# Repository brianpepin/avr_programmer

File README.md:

# AVR Programmer
Eagle files and gerbers for a programmer designed for Microchip's series of AVR microcontrollers. There is also a KiCad variant in the kicad directory, but I haven't tried it yet.  It was ported from Eagle and I re-routed the board.

## Overview
Microchip's series of AVR chips are simple 8 bit microcontrollers often used in Arduino boards. This programmer board can be used to program fuses and flash for bare AVR chips.

## Features

* Compatible with USBASP firmware and features, including slow clock.
* Selectable target voltage of 3.3v, 5v, or target provided (1.8v - 5.5v).
* Built-in serial to USB converter.
* Board can remain connected to target after programming.
* USB-C interface to PC with full ESD and overload protection.

## Design

This board is based on the hardware design for [USBASP](https://www.fischl.de/usbasp/) and is 100% compatible wth the USBASP firmware. I designed it to support different target voltages (namely 3.3v) and wanted built-in serial IO so I could connect a single connector to boards I design.

The board shows up as two USB devices: a FTDI serial port and a USBASP programmer.  There is an on-board USB hub that exposes both devices.  Target voltage is selectable through the VTARG switch and has three values:

1. 5V (left): Provide 5 volts as power and logic levels to the target board.
1. Float (middle): Adapt to whatever voltage the target board is using.
1. 3.3V (right): Provide 3.3 volts as power and logic levels to the target board.

If your board provides voltage of its own make sure you keep VTARG in the middle position.

The different voltage levels are shifted through an array of level shifters.  This circuit will change direction of the signals if PGM is bridged, which allows for initial programming of the board. All connections other than TXD and RXD also go to a high-impedance state whenever the red programming light is off (I reuse that signal line so I don't need any modifications to the USBASP firmware). Signal direction and tri-state is controlled by discrete logic, again so no USBASP mods are needed.  The level shifters I'm using go to high-impedance state when VCCA or VCCB is grounded.  This is handled by a push-pull pair of mosfets driven by discrete logic.

## Programming

Once the board is complete it must be flashed with the USBASP code. You need another working programmer for this.

1. Bridge the PGM pins on the board and set VTARG to either 5v or 3.3v depending on the output voltage of your existing programmer.
1. Connect your existing programmer's connector to the board.
1. Set your programmer to use a slow clock.
1. Run 'make Makefile88 fuses' from the USBASP project.
1. You can now turn off the slow clock feature of your programmer.
1. Run 'make Makefile88" to flash the firmware.

If successful, a green LED should be lit on the board. This LED is controlled by the USBASP firmware so it's a good indicator everything's working.  Remove the bridge to PGM and you should be good to go.

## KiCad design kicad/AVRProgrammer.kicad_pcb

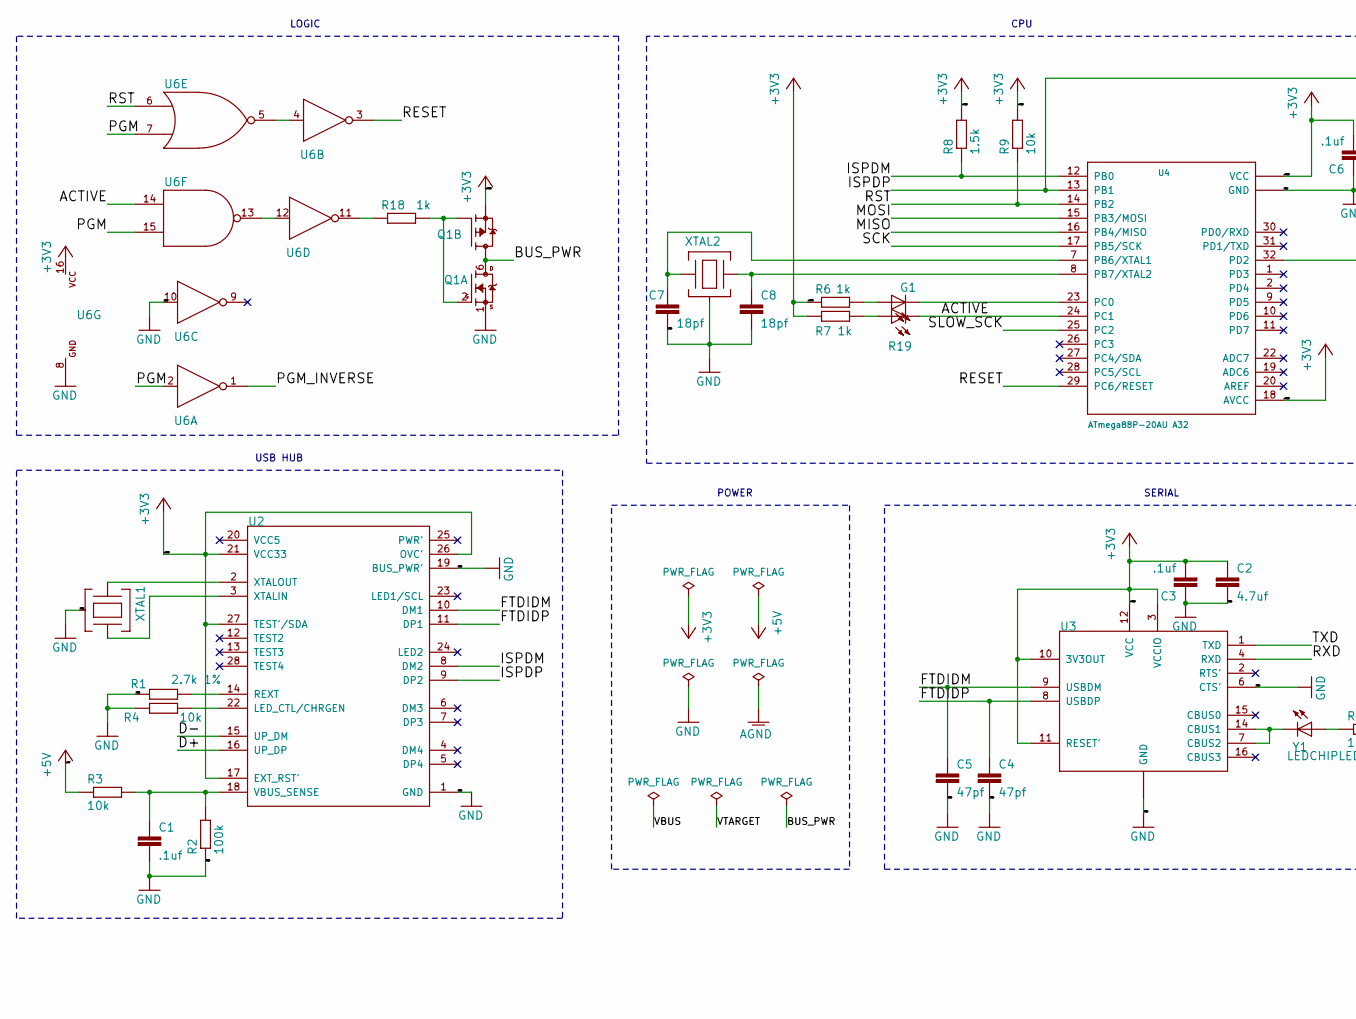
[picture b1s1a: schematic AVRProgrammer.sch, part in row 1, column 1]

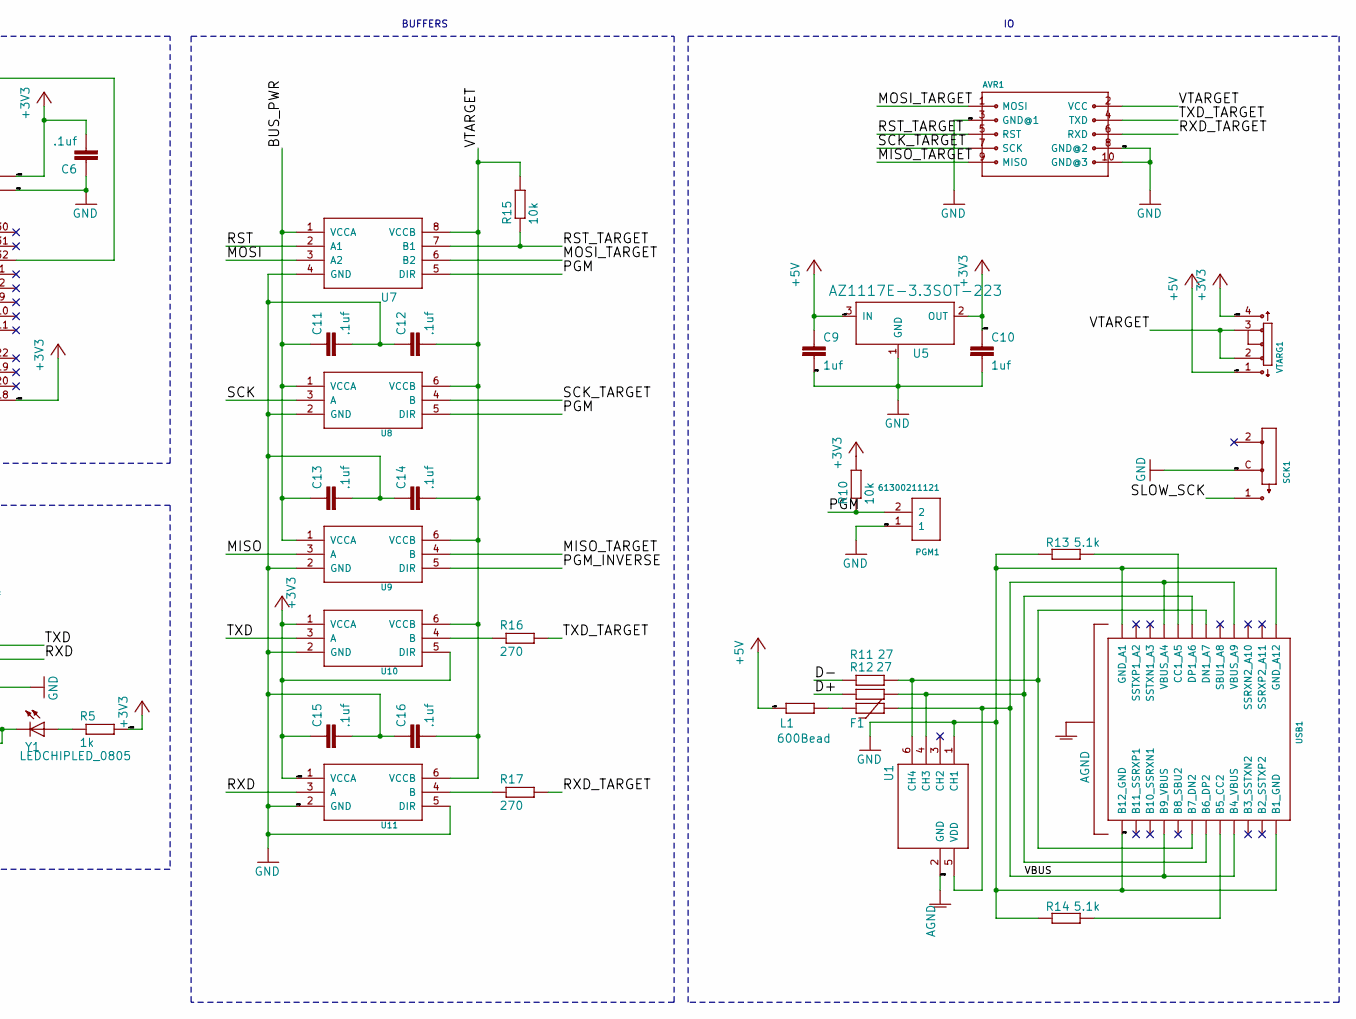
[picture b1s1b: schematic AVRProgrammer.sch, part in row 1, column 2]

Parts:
AVR1: 10PIN_ISP10PIN_ISP_RT; 10PIN_ISP_RT
C1, C3, C6, C11, C12, C13, C14, C15, C16: .1uf; C0805
C2: 4.7uf; C0805
C4, C5: 47pf; C0805
C7, C8: 18pf; C0805
C9, C10: 1uf; C0805
F1: MF-PSHT035KX-2; FUSC2113X120N
G1: SM0805GCL; CHIPLED_0805
L1: 600Bead; M0805
PGM1: 61300211121
Q1: SI1016CX-T1-GE3SOT-563F; SOTFL50P160X60-6N
R1: 2.7k 1%; M0805
R2: 100k; M0805
R3, R4, R9: 10k; M0805
R5, R6, R7, R18: 1k; M0805
R8: 1.5k; M0805
R10, R15: 10k; R0805
R11, R12: 27; M0805
R13, R14: 5.1k; M0805
R16, R17: 270; R0805
R19: SM0805HCL; CHIPLED_0805
SCK1: SPDT_SWITCH; SSAJ110100
U1: D5V0F4U6SO; SOT95P280X145-6
U2: XR22404SSOP28; SOP63P599X173-28
U3: FT230XSSOP16; SOP63P599X175-16
U4: ATmega88P-20AU A32; QFP80P887X887X120-32
U5: AZ1117E-3.3SOT-223; SOT230P700X180-4
U6: CD4572UB; SOP65P640X110-16N
U7: SN74LVC2T45-Q1VSSOP-8; SOP50P310X90-8N
U8, U9, U10, U11: SN74LVC1T45DRL; SOTFL50P160X60-6N
USB1: USBC_FEMALEUJ31-CH-G2-SMT-TR; USBC_UJ31-CH-G2-SMT-TR
VTARG1: SP3T_SWITCH; EG1315AA
XTAL1, XTAL2: XTAL_ABM8AIG; XTAL_SMT_3.2X2.5
Y1: LEDCHIPLED_0805; CHIPLED_0805

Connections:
+3V3: C2.1, C3.2, C6.2, C10.1, C15.1, Q1.4 (S), R5.2, R6.1, R7.1, R8.2, R9.2, R10.2, U2.17 (EXT_RST'), U2.21 (VCC33), U2.26 (OVC'), U2.27 (TEST'/SDA), U3.3 (VCCIO), U3.10 (3V3OUT), U3.11 (RESET'), U3.12 (VCC), U4.4 (VCC), U4.6 (VCC), U4.18 (AVCC), U5.2 (OUT), U6.16 (VCC), U10.1 (VCCA), U10.5 (DIR), U11.1 (VCCA), VTARG1.4
+5V: C9.1, L1.1, R3.1, U5.3 (IN), VTARG1.1
/ACTIVE: R19.C, U4.24 (PC1), U6.14 (I0)
/BUS_PWR: C11.1, C13.1, Q1.3 (D), Q1.6 (D), U7.1 (VCCA), U8.1 (VCCA), U9.1 (VCCA)
/D+: R12.1, U2.16 (UP_DP)
/D-: R11.1, U2.15 (UP_DM)
/FTDIDM: C5.1, U2.10 (DM1), U3.9 (USBDM)
/FTDIDP: C4.1, U2.11 (DP1), U3.8 (USBDP)
/ISPDM: R8.1, U2.8 (DM2), U4.12 (PB0)
/ISPDP: U2.9 (DP2), U4.13 (PB1), U4.32 (PD2)
/MISO: U4.16 (PB4/MISO), U9.3 (A)
/MISO_TARGET: AVR1.9 (MISO), U9.4 (B)
/MOSI: U4.15 (PB3/MOSI), U7.3 (A2)
/MOSI_TARGET: AVR1.1 (MOSI), U7.6 (B2)
/PGM: PGM1.2, R10.1, U6.2 (A), U6.7 (I1), U6.15 (I1), U7.5 (DIR), U8.5 (DIR)
/PGM_INVERSE: U6.1 (Y), U9.5 (DIR)
/RESET: U4.29 (PC6/RESET), U6.3 (Y)
/RST: R9.1, U4.14 (PB2), U6.6 (I0), U7.2 (A1)
/RST_TARGET: AVR1.5 (RST), R15.1, U7.7 (B1)
/RXD: U3.4 (RXD), U11.3 (A)
/RXD_TARGET: AVR1.6 (RXD), R17.2
/SCK: U4.17 (PB5/SCK), U8.3 (A)
/SCK_TARGET: AVR1.7 (SCK), U8.4 (B)
/SLOW_SCK: SCK1.1, U4.25 (PC2)
/TXD: U3.1 (TXD), U10.3 (A)
/TXD_TARGET: AVR1.4 (TXD), R16.2
/VBUS: F1.2, U1.5 (VDD), USB1.A4 (VBUS_A4), USB1.A9 (VBUS_A9), USB1.B4 (B4_VBUS), USB1.B9 (B9_VBUS)
/VTARGET: AVR1.2 (VCC), C12.2, C14.2, C16.2, R15.2, U7.8 (VCCB), U8.6 (VCCB), U9.6 (VCCB), U10.6 (VCCB), U11.6 (VCCB), VTARG1.2, VTARG1.3 (C)
AGND: U1.2 (GND), USB1.SHD$1 (SHLD), USB1.SHD$2 (SHLD), USB1.SHD$3 (SHLD), USB1.SHD$4 (SHLD)
GND: AVR1.3 (GND@1), AVR1.8 (GND@2), AVR1.10 (GND@3), C1.2, C2.2, C3.1, C4.2, C5.2, C6.1, C7.2, C8.2, C9.2, C10.2, C11.2, C12.1, C13.2, C14.1, C15.2, C16.1, PGM1.1, Q1.1 (S), R1.1, R2.1, R4.1, R13.1, R14.1, SCK1.C, U1.1 (CH1), U2.1 (GND), U2.19 (BUS_PWR'), U3.5 (GND), U3.6 (CTS'), U3.13 (GND), U4.3 (GND), U4.5 (GND), U4.21 (GND), U5.1 (GND), U6.8 (GND), U6.10 (A), U7.4 (GND), U8.2 (GND), U9.2 (GND), U10.2 (GND), U11.2 (GND), U11.5 (DIR), USB1.A1 (GND_A1), USB1.A12 (GND_A12), USB1.B1 (B1_GND), USB1.B12 (B12_GND), XTAL1.2 (CASE), XTAL1.4 (CASE), XTAL2.2 (CASE), XTAL2.4 (CASE)
unnamed: C1.1, R2.2, R3.2, U2.18 (VBUS_SENSE)
unnamed: C7.1, U4.7 (PB6/XTAL1), XTAL2.1
unnamed: C8.1, U4.8 (PB7/XTAL2), XTAL2.3
unnamed: F1.1, L1.2
unnamed: G1.A, R6.2
unnamed: G1.C, U4.23 (PC0)
unnamed: Q1.2 (G), Q1.5 (G), R18.2
unnamed: R1.2, U2.14 (REXT)
unnamed: R4.2, U2.22 (LED_CTL/CHRGEN)
unnamed: R5.1, Y1.A
unnamed: R11.2, U1.6 (CH4), USB1.A7 (DN1_A7), USB1.B7 (B7_DN2)
unnamed: R12.2, U1.4 (CH3), USB1.A6 (DP1_A6), USB1.B6 (B6_DP2)
unnamed: R13.2, USB1.A5 (CC1_A5)
unnamed: R14.2, USB1.B5 (B5_CC2)
unnamed: R16.1, U10.4 (B)
unnamed: R17.1, U11.4 (B)
unnamed: R18.1, U6.11 (Y)
unnamed: R7.2, R19.A
unnamed: U2.2 (XTALOUT), XTAL1.1
unnamed: U2.3 (XTALIN), XTAL1.3
unnamed: U3.7 (CBUS2), U3.14 (CBUS1), Y1.C
unnamed: U6.4 (A), U6.5 (O)
unnamed: U6.12 (A), U6.13 (O)

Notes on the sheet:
BUFFERS
CPU
SERIAL
USB HUB
LOGIC
POWER

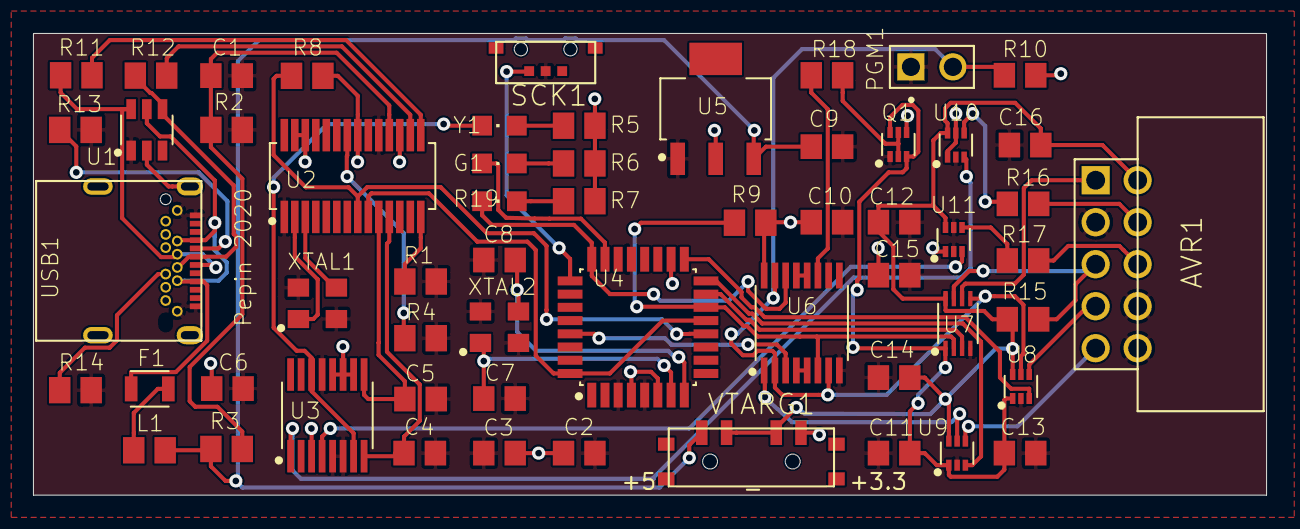
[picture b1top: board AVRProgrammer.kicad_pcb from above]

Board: 2 copper layers, 74.6 x 27.9 mm, 58 parts (0 on the bottom side), 53 nets.

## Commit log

2019-12-10 Initial populate
2019-12-11 Spelling
2020-02-23 Replace incorrect USB ESD component
2020-09-06 Missing pepin library
2020-09-06 Add KiCad version
